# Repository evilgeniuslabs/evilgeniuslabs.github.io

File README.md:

# Evil Genius Labs

This repository contains the source code for the [evilgeniuslabs.org](http://www.evilgeniuslabs.org) web site.

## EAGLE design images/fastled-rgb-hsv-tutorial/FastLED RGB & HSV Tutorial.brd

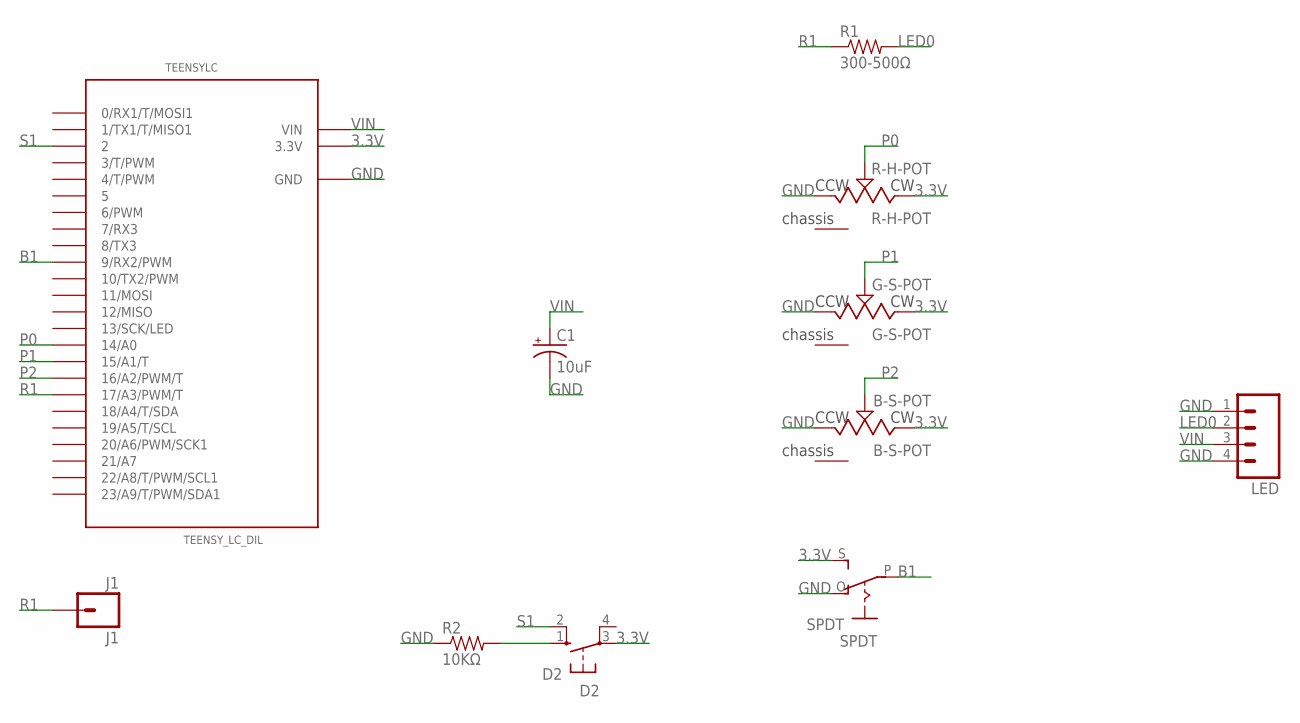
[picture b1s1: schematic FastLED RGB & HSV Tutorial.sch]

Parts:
B-S-POT: B-S-POT; PTV09A-4
C1: 10uF; CPOL-RADIAL-10UF-25V-KIT
D2: D2; B3F-10XX
G-S-POT: G-S-POT; PTV09A-4
J1: J1; 1X01
LED: M04PTH; 1X04
R1: 300-500Ω; AXIAL-0.1EZ
R2: 10KΩ; AXIAL-0.1EZ
R-H-POT: R-H-POT; PTV09A-4
SPDT: SPDT; EG1218
TEENSYLC: TEENSY_LC_DIL; TEENSY3-DIL

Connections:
3.3V: B-S-POT.3 (CW), D2.3, G-S-POT.3 (CW), R-H-POT.3 (CW), SPDT.S, TEENSYLC.3.3V
B1: SPDT.P, TEENSYLC.9 (9/RX2/PWM)
GND: B-S-POT.1 (CCW), C1.2 (-), G-S-POT.1 (CCW), LED.1, LED.4, R2.P$1 (1), R-H-POT.1 (CCW), SPDT.O, TEENSYLC.AGND (GND), TEENSYLC.GND; also elsewhere on the board
LED0: LED.2, R1.P$2 (2)
unnamed: D2.1 (S), R2.P$2 (2)
P0: R-H-POT.2 (WIPER), TEENSYLC.14/A0
P1: G-S-POT.2 (WIPER), TEENSYLC.15/A1 (15/A1/T)
P2: B-S-POT.2 (WIPER), TEENSYLC.16/A2 (16/A2/PWM/T)
R1: J1.1, R1.P$1 (1), TEENSYLC.17/A3 (17/A3/PWM/T); also elsewhere on the board
S1: D2.2 (S1), TEENSYLC.2
VIN: C1.1 (+), LED.3, TEENSYLC.VIN

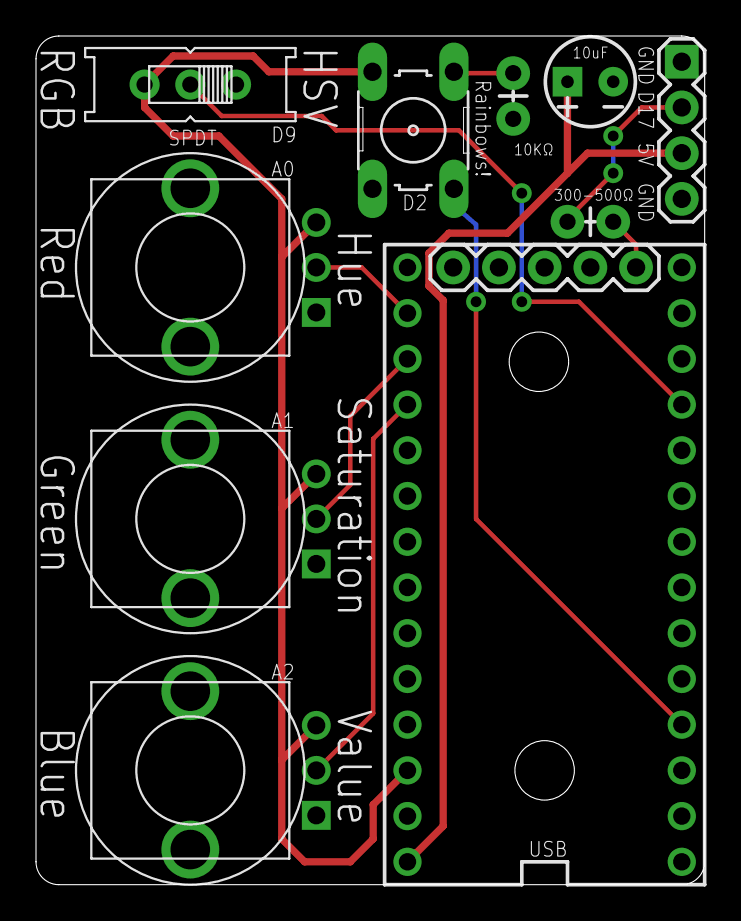
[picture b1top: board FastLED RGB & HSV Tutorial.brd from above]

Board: 2 copper layers, 37.1 x 47.1 mm, 13 parts (0 on the bottom side), 11 nets.

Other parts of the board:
J6: 1X05
U$1, U$3: STAND-OFF

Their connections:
GND: J6.3; also elsewhere on the board
R1: J6.1; also elsewhere on the board

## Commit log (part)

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2017-04-19 Added jekyll redirects.
2017-04-20 Updated site
2017-04-24 Updated site.
2017-04-28 Added new animated logo.
2017-05-26 Removed vines.
2017-05-27 Added mini wifi led controller.
2017-05-27 Added FastLED Arcade post
2017-05-27 Added source code link
2017-06-02 Added Psilocybe post.
2017-06-02 Updated Psilocybe post.
2018-01-05 Fixed copyright year.
2018-01-20 Fixed 'Arduino ESP8266 filesystem uploader' link.
2018-03-02 Added ESP32 FeatherWing
2018-03-02 Added power info to level shifter featherwing post.
2018-03-02 Rename 2018-02-21-level-shifter-featherwing.md to 2018-03-01-level-shifter-featherwing.md
2018-04-03 Added octo featherwing assembly instructions
2018-04-22 Fixed Eclipse v2 images.
2018-04-22 Fixed Eclipse v2 video.
2018-04-22 Fixed Eclipse v2 thumbnail.
2018-04-22 Fixed Eclipse v2 image width.
2018-08-01 Added Wemos D32 Level Shifter Shield.
2018-08-14 Updated product links, added JST links.
2018-08-14 Added ESP32 DevKitC page.
2018-09-08 Added NodeMCU-32S shield page.
2018-09-08 Made ESP32 shield pages more consistent.
2018-10-21 Updated NodeMCU-32S instructions
2018-10-27 Added Hexadecimal (16 output) NodeMCU-32S Wi-Fi and BLE LED Controller
2018-10-28 Added youtube video for hexadecimal nodemcu-32s shield.
2018-11-07 Added Trinket Pro RGB LED Micro Quadrotor Race Gate
2018-11-07 Updated race gate post.
2018-11-07 Fixed race gate 3D printed part images.
2018-11-09 Added hexadecimal wemos d32 shield.
2018-11-09 Updated all resistors to 330 Ohm.
2018-11-12 Added multigp tiny whoop class 19x19" gate.
2018-11-12 Updated race gate pages.
2018-12-16 Added post date and tinyurl.
2019-02-20 Added 6 output Wemos D1 Mini shield post.
2019-02-20 Fixed GitHub icon.
2019-03-24 Added Thingiverse link to Wemos D1 Mini shield enclosure. Switched a bunch of links and images from http to https.
2019-03-24 Updated footer
2019-04-14 Added FAQ section
2019-04-27 Fixed Wemos D1 Mini links.
2019-05-26 Updated logo.
2019-05-27 Added Nano v3 shield.
2019-05-27 Updated race gate posts.
2019-06-26 Fixed post TOCs.
2019-11-09 Added instructions and pics for the mini shield.
2019-11-09 Added fpv faq
2019-12-04 More FAQ page improvements
2019-12-11 Updated about page.
2019-12-11 Updated social media links.
2020-01-01 Added featherwing pinouts
2020-01-01 Fixed TOCs
2020-01-02 level shifter breakouts: unpublish and fix link
2020-01-20 Added smd-mini-six-output-esp8266-wi-fi-rgb-led-controller
2020-01-20 Published smd-mini-six-output-esp8266-wi-fi-rgb-led-controller
2020-01-20 Fix TOC
2020-01-21 Updated Fibonacci64
2020-02-02 Add f64 redirect to fibonacci64
2020-02-16 fibonacci64 playlist
2020-02-29 Added Fibonacci256 post
2020-02-29 Updated F256 media
2020-02-29 F256 youtube playlist link
2020-02-29 F256 playlist
2020-02-29 Added header links to instructions.
2020-03-06 Added parts sections to f64 and f256
2020-03-08 Added F128, updated F256.
2020-03-14 Added more ElectroMage Pixelblaze info, maps, gifs
2020-03-14 Condense f128 images and pb maps.
2020-03-16 Added f128 pixelblaze x, y, a map
2020-04-20 Create CNAME
2020-04-20 Update CNAME
2020-07-15 Fixed some typos (distrubution). Added Fibonacci boards to both portfolio and products. Added F32Mini & F64Mini drafts. Reorganized posts.
2020-07-26 Added new f256 pride gif
2020-07-28 Fixed f256 TOC.
2020-07-30 Updated f64 gif
2020-07-30 Fixed the TOC, again.
2020-08-02 Added Color Waves Playground post.
2020-08-04 Added F256 open case info. Fixed web app image links.
2020-08-09 f64 open case info
2020-08-10 Added connection instructions for fully assembleds
2020-08-14 Updated/fixed links.
2020-08-29 Publish f32mini. Publish IcosaLEDron draft.
2020-09-04 More d20 assembly instructions & pics.
2020-10-10 Added F64 Pixelblaze map. Fixed broken TOCs again.
2020-11-03 Update contact form.
2020-11-07 Fix f64mini code link and details.
2020-12-16 Updated FPV FAQ
2021-01-05 Fixed typo.
2021-01-15 Add TLDR to shields FAQ.
2021-01-31 Added sol-v2.
2021-01-31 Published sol-v2
2021-02-06 Fixed macrochip image
2021-02-06 Added more macrochip details.
2021-02-07 Added Atmel ATxmega32E5
2021-02-07 Added credit link.
2021-02-07 Added Sun Ultra SPARC III Moved macrochip data to yml file Generate collection from macrochip yml file
2021-02-07 Fix gif
2021-02-11 Added more macrochips
2021-02-14 Added Allwinner A13 Intel i486 DX2-66 MediaTek MT7688AN
2021-02-14 Added RealTek RTL2832U
2021-02-20 AMD K6-2 500AFX IBM PowerPC 604e MOS Technology 6502AD Motorola 68HC11
2021-02-20 Fix AMD K6-2 500AFX image
2021-02-20 Swap ESP32-PICO-D4 image
2021-02-20 Apple A11
2021-02-23 STM32F407-VGT6
2021-02-23 ST10F168-Q6
2021-02-24 IBM Gekko - Nintendo GameCube CPU Intel i486 DX-33 Sony PlayStation 2 GraphicsSynthesizer
2021-02-26 Xilinx Artix-7 Zilog Z80
2021-02-26 Atmel ATmega8A Zilog Z80A
2021-02-27 Nvidia GeForce 256
2021-02-28 Change button style.
2021-03-03 Creative Technology Sound Blaster VIBRA 16 CT2502 Digital StrongArm SA-110S Hitachi SH-2 HD6417095 (Sega Saturn, Sega 32X and Capcom CP System III) Intel i860 XR-33 Microchip Technology Microsemi Pol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
2021-03-03 Altera Cyclone V FPGA Broadcom BCM2836 Raspberry Pi 2 Model B CPU Lattice Semiconductor ECP5-5G FPGA Motorola 68000 (m68k) Nintendo DS CPU NTR Skytraq Venus838LPx-T-L GPS Receiver Sony PlayStation CP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
2021-03-04 Xilinx XC216 (XC6200)
2021-03-08 Atmel AT90S8535 CSG 8500 Signetics NE555N STM32F405-RGT6
2021-03-10 Altera Max 10 Atheros AR9170 Intel i386 SX-25 Linear Technology LTC2208 Ralink RT2560F
2021-03-12 Intel D8086-2
2021-03-13 Motorola MC68030FE20 Nordic Semiconductor nRF52832 Nordic Semiconductor nRF52840 Texas Instruments CC2531 Zigbee Texas Instruments CC2540 BLE
2021-03-13 Added macrochip design count.
2021-03-16 Espressif ESP32-D0WDQ6 NXP SPC5748GHMKU6 STM32F103-C8T6
2021-03-19 HPE iLO 88PA0SA1-BUY2 Reticon SAD1024 BBD (Bucket Brigade Device) Analog Delay/Flanger
2021-03-20 Broadcom Trident+ BCM56842A1IFRBG
2021-03-25 Atmel ATmega1284
2021-03-26 AMD Ryzen Threadripper 1920X
2021-03-27 Espressif ESP32-S2
2021-03-27 AMD Ryzen 7 I700X STM32F042C6U6
2021-03-31 F32 THT kit draft
2021-04-01 Fixed F32 THT Kit specifications. More work on assembly instructions.
2021-04-01 Reworked LED order checklist
2021-04-05 HP PA-8000 (PCX-U) Onyx
2021-04-10 Altera Max 10 - 10M50DAF484C7G Cyrix 5x86-100GP IBM Blue Lightning DX2
2021-04-13 Analog Devices AD9361BBCZ FTDI FT2232H-56Q Samsung K4P4G324EB-AGC1 (Raspberry Pi RAM) SMSC USB4604 STM32F072C8U6 STM32L562ZET6 Sun UltraSPARC II Xilinx Kintex-7 Xilinx Versal Xilinx Virtex UltraScale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
2021-04-24 nRF52840 (AND!XOR custom edition)
2021-05-12 More F32 THT Kit instructions progress. Added F64 Micro & F512 drafts.
2021-05-12 Fix F32 THT Kit TOC
2021-05-15 Update and publish f64micro & f32kit
2021-05-26 Updates.
2021-05-28 F32 kit updates.
2021-06-11 Added new macrochips: Apple A14 Intel Pentium 75 Microchip PIC32MZ2048EFM100-I/PT MOS 6502 (4" square version) SiFive FE310-G000 STM32L062K8T6
2021-06-11 Fixed macrochips page.
2021-06-12 Added Macrochips: * SpaceX Drone Ship - Of Course I Still Love You * SpaceX Landing Pad - Of Course I Still Love You
2021-06-17 Updated & published F512 Publish F64 Mini
2021-07-07 Added some page aliases.
2021-07-14 Xilinx Spartan-6
2021-08-04 Updated f65 micro. Fixed TOCs. Again.
2021-08-05 Minor edits.
2021-08-19 Added macrochips: STLS2F02 Loongson & ZTEIC Z8H172T Added/updated Fibonacci connection instructions.
2021-08-27 Add f64 nano draft.
2021-08-29 Add F64 Micro acrylic case asssembly instructions.
2021-09-09 Update f64 micro & nano. Added Sony PlayStation 5 SoC macrochip.
2021-09-14 Update F64 Nano Add Kraken draft
2021-09-21 Update f64 nano source code link
2021-09-22 Added f64nano case assembly instructions, fixed ToC.
2021-09-22 Reorder images.
2021-10-02 Added Kraken code & assmebly instructions.
2021-10-02 Added macrochip: Intel i386 EX-25
2021-10-16 Added Chamaeleon64
2021-10-25 Add c64 redirects.
2021-10-25 Add 404 page.
2021-10-28 Added Raspberry Pi RP3A0 - Zero 2 W SiP (Broadcom BCM2710A1)
2021-11-17 More post details.
2021-11-19 Added macrochips.
2021-11-24 Added more macrochip updates.
2021-12-05 Added macrochips
2022-01-26 Added ifixit labels post.
2022-01-26 Added link to mako kit.
2022-01-30 Added Xilinx Zynq - XC7Z010
2022-03-26 Added F64 Micro HDR post draft.
2022-03-26 Updated f64 micro hdr pixelblaze map.
2022-03-27 Added note to reduce Pixelblaze global brightness.
2022-04-11 New macrochips: - Motorola MC68000P8 - Zilog Z084008PSC
2022-04-13 Axis ARTPEC-8 macrochip
2022-04-17 Fibonacci 182 Card
2022-04-29 Added Fibonacci64x50mm (goggles). Fixed F182 card post.
2022-04-29 Updated Fibonacci64x50mm (goggles).
2022-05-01 F64 goggle & F182 card updates.
2022-05-07 Added f1024 post. Sort product & portfolio drop down lists. Added custom sort keys to posts. Fix aspect ratio for responsive embeds. Set loading to lazy for embeds.
2022-05-08 Add f64 flower post.
2022-05-08 Fixed f64 flower pics
2022-05-10 Added F256x75mm post
2022-05-10 Added f256x75mm image.
2022-05-14 Added Apple A12 & A13
2022-07-01 Fixed f256 pixelblaze map.
2022-08-19 Added f256 & f512 pixelblaze posts, images.
2022-09-02 Update F256pb post.
2022-09-10 Fix lux lavalier post
2022-09-10 Condense header images in F64 & F256
2022-09-14 Added F256HDR post.
2022-09-17 Updated LL buy header
2022-10-01 Update CycloHex
2022-10-20 Fix links.
2022-11-05 Updated mastodon profile. Added F64 Flower assembly instructions.
2022-12-17 Added Mega CycloHex with 39mm LED rings. Added F256 Pixelblaze retrofit parts & instructions. Fixed Cyclohex post excerpt.
2022-12-17 Added laser cut acrylic part preview images. Fixed black LED acrylic link.
2022-12-18 Added Pixelblaze XYZ map for tree-v2
2023-01-03 Updated social link icons. Updated about page.
2023-01-04 Remove Etsy macrochip link
2023-02-04 Added Nintendo Gameboy Advance CPU (CPU AGB)
2023-02-11 Improve macrochip layout
2023-03-25 Added buy link to F256 HDR + PB
2023-04-10 Fix F64 Micro HDR code link
2023-07-06 Added more social links.
2023-07-23 Add Fibonacci HDR Heart Updated other posts
2023-08-01 Added f128 flex
2023-08-13 Lazy load poster images. Remove vine code.
2023-09-07 Heart updates
2023-09-08 Heart instructions
2023-09-08 Renamed ifixit post.
2023-09-08 ifixit post redirect
2023-10-11 Added F256 Pixelblaze patterns. Added iFixit Minnow label files.
2023-10-29 Updated one inch f128 code link
2023-12-29 Updated F64 nano page
2024-02-09 F512 HDR PB
2024-03-23 Add F48x14mm
2024-03-26 Add 1" F32 & 1" F64
2024-03-29 Add F128 HDR 86mm
2024-05-04 Add WCH CH446Q macrochip
2024-05-04 Update WCH CH446Q macrochip
2024-06-04 Necklace Battery Holder USB-C
2024-06-18 Add oEmbed / OpenGraph tags
2024-09-01 ublox M8 & M9
2024-09-01 Macrochip: Raspberry Pi RP2350
2024-10-01 Cube enclosure instructions and downloads
2024-10-04 Cube instructions updates
2024-10-11 Cube updates
2024-11-14 Cube 8 updates.
2024-11-14 Update cube8 categories
2024-11-15 Remove the last traces of xitter. Rework some pages.
2024-11-20 Move some product store links from Tindie to Lectronz.
2024-11-28 Update 8 cube acrylic instructions.
2024-11-29 Rework LED Cube 8x8x8 section headings
2024-11-30 Fix video thumbnails taking over fullscreen on iOS.
2025-01-24 Add missing LED Cube 8x8x8.pbb file
2025-03-21 Add grid, remove threads
2025-04-23 Invert F512pb map y axis
2025-04-27 Add PixelBlaze map for 1" F128
2025-07-16 Update 1f128, add case options.
2025-07-16 Fix 1f128 images, add links.
2025-07-16 Fix 1f128 images
2025-08-07 Add tutorials section. Add 3D Pixelblaze tutorial. Retire some products. Add retired products section. Remove Tindie store links, replace with Lectronz. Add links to OSH Park for retired level shifte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
2025-08-07 Remove invalid tree-v2 imgurId
2025-08-08 Pixelblaze 3D Tutorial - Part 2
2025-08-11 Fix more links.
2025-10-16 Remove old store links
2025-11-15 Dark slate theme
2025-11-15 Fix static images
2025-11-17 Move images from imgur to github
2025-11-17 Fixes
2025-12-02 Add more missing images.
2025-12-12 Update 1f128 docs.
2025-12-13 Update 1" Fibonacci instructions.
2026-02-03 Add Fibonacci256 Expanding HDR
2026-02-11 Add F48 14mm pinout.
2026-04-15 Add F256eh pbb backup

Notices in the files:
parts and their libraries:
SparkFun-Connectors: Licensing: Creative Commons ShareAlike 4.0 International - https://creativecommons.org/licenses/by-sa/4.0
